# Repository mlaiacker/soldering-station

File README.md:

# Soldering Station for Weller Soldering Tips

https://www.weller-tools.com/eu/de/industrielles-loeten/produkte/loetspitzen/rtm-013-s

Power or Battery supply 10-14V DC up to 3A or so needed.

This project is based on the work of Martin Kumm.

http://www.martin-kumm.de/wiki/doku.php?id=05Misc:SMD_Solderstation

I made it simpler and cheaper. Instead of using an Arduino I use a ATmega8. This design doesn't use SMD instead a single sided PCB for easy assembly and cheap PCB production. The PCB is only 70x50mm. Instead of using two buttons to adjust the temperature I use a poti and optionally you can use a standard HD44780 compatible LCD to display temperatures. It runs on plain c (no arduino) and also includes supports a bootloader for easy firmware upgrade. The Bootloader has to be programmed befor soldering the mega8 into the PCB. The bootloader is activaded using the Boot pins on the PCB (short PD2 to ground)

http://mlaiacker.mooo.com/Elektronik/Soldering%20Station/

http://fpv-community.de/showthread.php?41335-DIY-SMD-L%F6tstation-Ersatz-f%FCr-%28WELLER%29

## PCB layout

[board layout pdf hardware/eagle/rt_solder_simple_V1.2.brd.pdf](hardware/eagle/rt_solder_simple_V1.2.brd.pdf?raw=true)

## Bill of Materials for PCB

[BOM as pdf](hardware/eagle/rt_solder_simple_V1.2.BOM.pdf?raw=true)

| Qty | Value        | Device          | Package      | Parts                | Description                 | Comment                       | Link |
| --- | ------------ | --------------- | ------------ | -------------------- | --------------------------- | ----------------------------- | ---- |
| 3   | 10nF         | C-EU050-035X075 | C050-035X075 | C6, C7, C8           | CAPACITOR,                  |                               |      |
| 5   | 100nF        | C-EU050-035X075 | C050-035X075 | C3, C4, C9, C10, C11 | CAPACITOR,                  |                               |      |
| 1   | TLC27L2ACP   | TLC27L2ACP      | DIL08        | IC3                  | DUAL OPERATIONAL AMPLIFIERS |                               |      |
| 1   | 22µH or 10R  | L-EU0207/10     | 0207/10      | L1                   | INDUCTOR,                   |                               |      |
| 1   | BOOT         | JP1E            | JP1          | JP2                  | JUMPER                      | to enable bootloader          |      |
| 1   | MEGA8-P      | MEGA8-P         | DIL28-3      | IC1                  | MICROCONTROLLER             | needs bootloader              |      |
| 1   | 2N7000 N-CH  | VN2222KM        | TO237        | Q1                   | N-Channel MOSFET            |                               |      |
| 1   | IRF5305 P-CH | IRF9530         | TO220BV      | Q3                   | P-CHANNEL POWER-MOS-FET     |                               |      |
| 1   | LCD          | PINHD-2X7       | 2X07         | JP1                  | PIN HEADER                  | optional                      |      |
| 1   | LED          | MA03-1          | MA03-1       | SV4                  | PIN HEADER                  |                               |      |
| 1   | POTI         | MA03-1          | MA03-1       | SV1                  | PIN HEADER                  | Poti to set temperatur 1K-50K |      |
| 1   | UART         | MA03-1          | MA03-1       | SV2                  | PIN HEADER                  | optional                      |      |
| 1   | 4.7µF 10V    | CPOL-EUE2.5-6   | E2,5-6       | C1                   | POLARIZED CAPACITOR         |                               |      |
| 2   | 470µF 16V    | CPOL-EUE3.5-10  | E3,5-10      | C2, C5               | POLARIZED CAPACITOR,        |                               |      |
| 1   | 100R         | R-EU_0207/10    | 0207/10      | R6                   | RESISTOR,                   |                               |      |
| 1   | 470R         | R-EU_0207/10    | 0207/10      | R2                   | RESISTOR,                   |                               |      |
| 1   | 68k          | R-EU_0207/10    | 0207/10      | R5                   | RESISTOR,                   |                               |      |
| 2   | 5k6          | R-EU_0207/10    | 0207/10      | R4, R7               | RESISTOR,                   |                               |      |
| 4   | 1k           | R-EU_0207/10    | 0207/10      | R3, R8, R11, R12     | RESISTOR,                   |                               |      |
| 1   | 47k          | R-EU_0207/10    | 0207/10      | bodge                | RESISTOR,                   | to fix tmperature measurement |      |
| 1   | 10M          | R-EU_0207/10    | 0207/10      | bodge                | RESISTOR,                   | to fix tmperature measurement |      |
| 1   | 10k          | R-EU_0207/10    | 0207/10      | bodge                | RESISTOR,                   | to add voltage measurement |      |
| 1   | 100k         | R-EU_0207/10    | 0207/10      | bodge                | RESISTOR,                   | to add voltage measurement |      |
| 1   | 78L05        | 78XXS           | 78XXS        | IC2                  | VOLTAGE REGULATOR           |                               |      |
| 1   | POWER        | W237-02P        | W237-132     | X1                   | WAGO SREW CLAMP             | optional                      |      |
| 1   | Solder       | W237-3E         | W237-3E      | X2                   | WAGO SREW CLAMP             | optional                      |      |

## Images

PCB<br>
 <br>
With nice enclosure and LCD<br>
 <br>
You can also just use this scale to set the temperature instead of the LCD
 <br>
Ask me for PCBs !! I had 10 made and some are available<br>
 <br>

## FAQ

### Hast du noch Platinen? 

ja noch: <br>
10 (2.4.2016)<br>
9 (5.4.2016)<br>
Ich kann auch gleich programmierten atmega8 und OPA und LCD dazu legen

### Was Kostet? 
10

### hex bauen?

```
make all
```

Das erstellen der main.hex geht über das Makefile mit "make all" dazu musst du den gcc avr Compiler installiert haben siehe dazu :http://www.mikrocontroller.net/articles/AVR-GCC

### flashen?

[for atmega 168](software/avr/main_atmega168.hex)

[for atmega 8](software/avr/main_atmega8.hex)

```
make program
```

Mit "make program" wird dann avrdude aufgerufen um über die serielle Schnittstelle ein neues Programm zu laden.
Dazu musst du wahrscheinlich den Port (com1) ändern im Makefile

```
AVRDUDE_PORT = com1 -b 38400 # programmer connected to serial device
```

Computer per TTL Seriell mit der Platine verbinden einen jumper auf die "Boot" pins stecken und einschalten dann wird der Bootloader aktiviert.

### bootloader ?

kopliziert. mit extra Adapter per ISP und dann mit "make programm_all" im bootloader Ordner. (avrdude und DIAMEX USB ISP bei mir)

### Wo bekomme ich IC3 her?

TLC 272 DIP bei reichelt

### Temperatur stimmt nicht

Die auf dem Display angezeigte Temperatur ist zu hoch bzw entspricht nicht der an der Lötspitze gemessenen. 
Bitte einen 47k Widerstand von Pin 3 an IC3 nach Masse löten und neue Software laden und wenn nötig
```C
#define TEMP_GAIN	(4980L)
#define TEMP_OFFSET	(-8)
```
anpassen.

 <br>

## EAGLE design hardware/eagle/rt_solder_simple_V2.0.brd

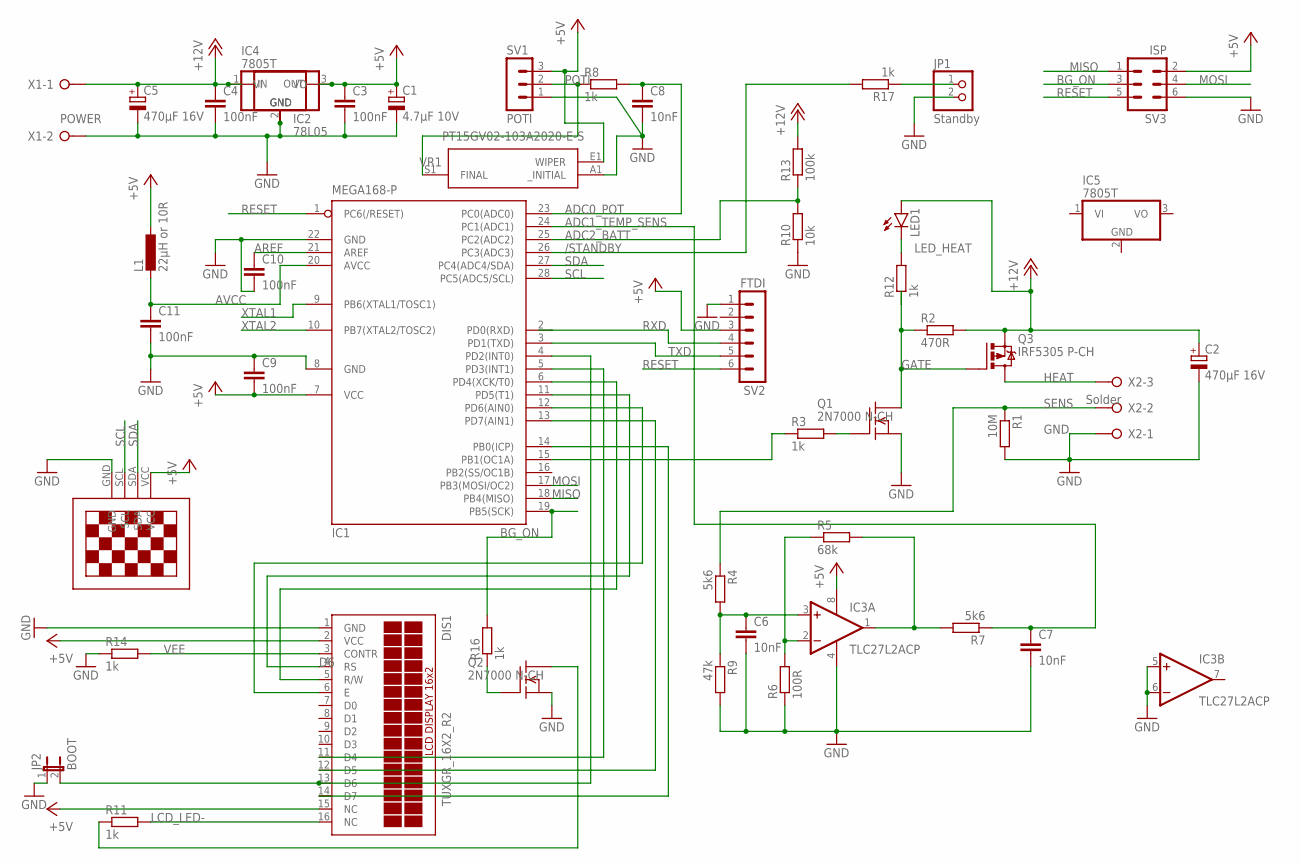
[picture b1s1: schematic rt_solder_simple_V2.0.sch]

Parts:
C1: 4.7µF 10V; E2,5-6
C2, C5: 470µF 16V; E3,5-10
C3, C4, C9, C10, C11: 100nF; C050-035X075
C6, C7, C8: 10nF; C050-035X075
DIS1: TUXGR_16X2_R2
IC1: MEGA168-P; DIL28-3
IC2: 78L05; 78XXS
IC3: TLC27L2ACP; DIL08
IC4, IC5: 7805T; TO220H
JP1: Standby; 1X02
JP2: BOOT; JP1
L1: 22µH or 10R; 0207/10
LED1: LED5MM
Q1, Q2: 2N7000 N-CH; TO237
Q3: IRF5305 P-CH; TO220BV
R1: 10M; 0207/10
R2: 470R; 0207/10
R3, R8, R11, R12, R14, R16, R17: 1k; 0207/10
R4, R7: 5k6; 0207/10
R5: 68k; 0207/10
R6: 100R; 0207/10
R9: 47k; 0207/10
R10: 10k; 0207/10
R13: 100k; 0207/10
SV1: POTI; MA03-1
SV2: FTDI; MA06-1
SV3: ISP; ML6
U$1: 13"OLED13"OLED; 1.3"OLED
VR1: PT15GV02-103A2020-E-S; PT15GV02103A2020ES
X1: POWER; W237-132
X2: Solder; W237-3E

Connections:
+5V: C1.+, C3.1, C9.2, DIS1.2 (VCC), IC1.7 (VCC), IC2.OUT, IC3.8 (VDD), IC4.3 (VO), L1.1, SV1.3, SV2.3, SV3.2, U$1.VCC, VR1.E1 (WIPER)
+12V: C2.+, C4.1, C5.+, IC2.IN, IC4.1 (VI), LED1.A, Q3.S, R2.2, R13.2, X1.1
/STANDBY: IC1.26 (PC3(ADC3)), R17.2
ADC0_POT: C8.1, IC1.23 (PC0(ADC0)), R8.2
ADC1_TEMP_SENS: C7.1, IC1.24 (PC1(ADC1)), R7.1
ADC2_BATT: IC1.25 (PC2(ADC2)), R10.2, R13.1
AREF: C10.1, IC1.21 (AREF)
AVCC: C11.1, IC1.20 (AVCC), L1.2
BG_ON: IC1.19 (PB5(SCK)), R16.2, SV3.3
D4: DIS1.11 (D4), IC1.5 (PD3(INT1))
D5: DIS1.12 (D5), IC1.13 (PD7(AIN1))
D6: DIS1.13 (D6), IC1.4 (PD2(INT0)), JP2.2
D7: DIS1.14 (D7), IC1.14 (PB0(ICP))
GATE: Q1.1 (D), Q3.G, R2.1, R12.1
GND: C1.-, C2.-, C3.2, C4.2, C5.-, C6.2, C7.2, C8.2, C9.1, C10.2, C11.2, DIS1.1 (GND), IC1.8 (GND), IC1.22 (GND), IC2.GND, IC3.4 (GND), IC3.5 (+IN), IC3.6 (-IN), IC4.2 (GND), JP1.2, JP2.1, Q1.3 (S), Q2.3 (S), R1.2, R6.1, R9.2, R10.1, R14.1, SV1.1, SV2.1, SV3.6, U$1.GND, VR1.A1 (_INITIAL), X1.2, X2.1
HEAT: Q3.D, X2.3
LCD_E: DIS1.6 (E), IC1.12 (PD6(AIN0))
LCD_LED-: DIS1.16 (NC), R11.2
LCD_RS: DIS1.4 (RS), IC1.11 (PD5(T1))
LCD_RW: DIS1.5 (R/W), IC1.6 (PD4(XCK/T0))
LED_HEAT: LED1.K (C), R12.2
MISO: IC1.18 (PB4(MISO)), SV3.1
MOSI: IC1.17 (PB3(MOSI/OC2)), SV3.4
unnamed: Q1.2 (G), R3.2
unnamed: C6.1, IC3.3 (+IN), R4.2, R9.1
unnamed: IC3.2 (-IN), R5.1, R6.2
unnamed: IC3.1 (OUT), R5.2, R7.2
unnamed: IC1.15 (PB1(OC1A)), R3.1
unnamed: Q2.2 (G), R16.1
unnamed: JP1.1, R17.1
unnamed: Q2.1 (D), R11.1
POTI: R8.1, SV1.2, VR1.S1 (FINAL)
RESET: IC1.1 (PC6(/RESET)), SV2.6, SV3.5
RXD: IC1.2 (PD0(RXD)), SV2.4
SCL: IC1.28 (PC5(ADC5/SCL)), U$1.SCL
SDA: IC1.27 (PC4(ADC4/SDA)), U$1.SDA
SENS: R1.1, R4.1, X2.2
TXD: IC1.3 (PD1(TXD)), SV2.5
VEE: DIS1.3 (CONTR), R14.2
XTAL1: IC1.9 (PB6(XTAL1/TOSC1))
XTAL2: IC1.10 (PB7(XTAL2/TOSC2))

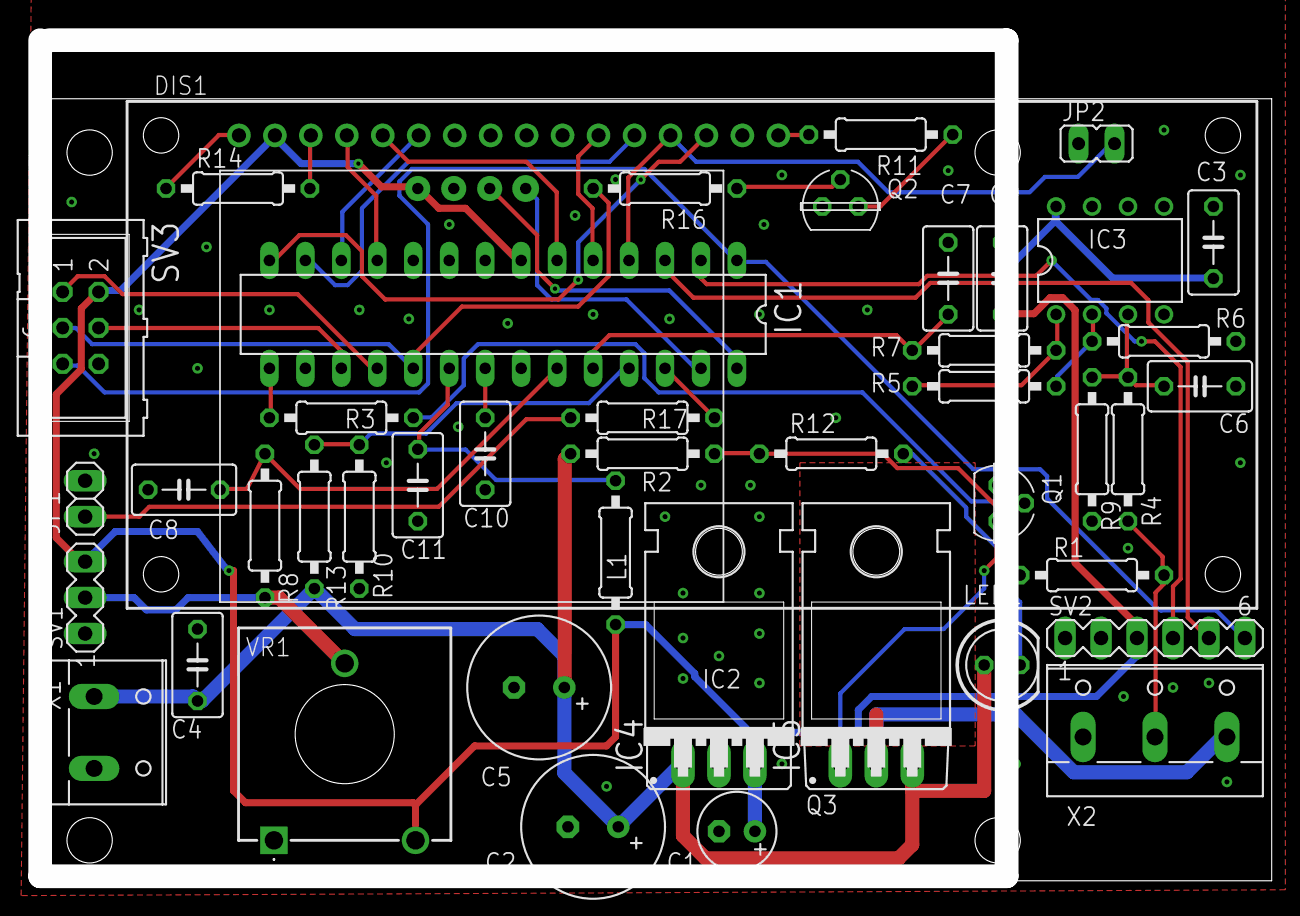
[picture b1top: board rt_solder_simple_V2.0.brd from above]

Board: 2 copper layers, 86.1 x 59.1 mm, 47 parts (0 on the bottom side), 39 nets.

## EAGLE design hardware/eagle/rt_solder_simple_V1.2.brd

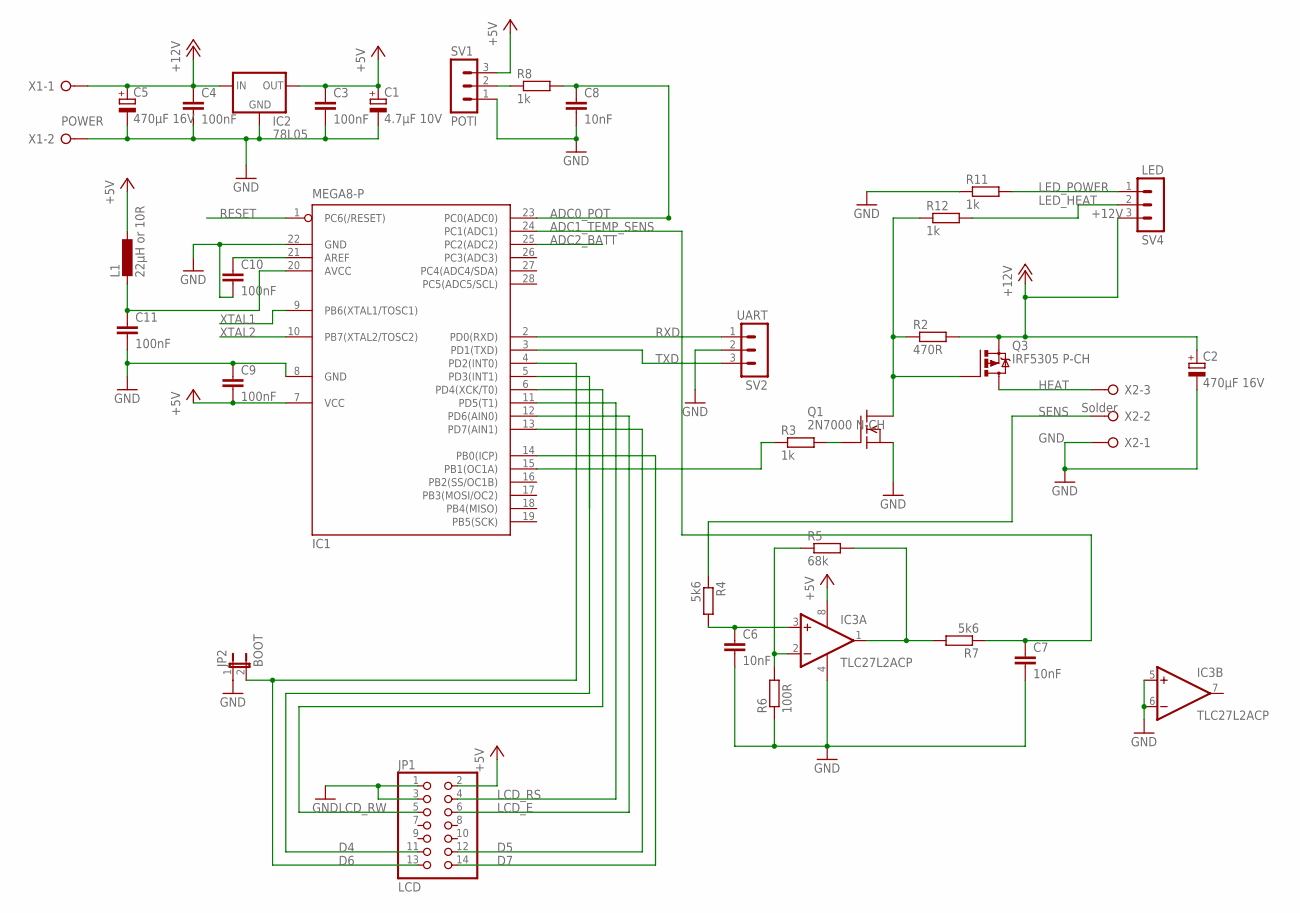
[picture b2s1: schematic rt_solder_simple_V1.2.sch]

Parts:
C1: 4.7µF 10V; E2,5-6
C2, C5: 470µF 16V; E3,5-10
C3, C4, C9, C10, C11: 100nF; C050-035X075
C6, C7, C8: 10nF; C050-035X075
IC1: MEGA8-P; DIL28-3
IC2: 78L05; 78XXS
IC3: TLC27L2ACP; DIL08
JP1: LCD; 2X07
JP2: BOOT; JP1
L1: 22µH or 10R; 0207/10
Q1: 2N7000 N-CH; TO237
Q3: IRF5305 P-CH; TO220BV
R2: 470R; 0207/10
R3, R8, R11, R12: 1k; 0207/10
R4, R7: 5k6; 0207/10
R5: 68k; 0207/10
R6: 100R; 0207/10
SV1: POTI; MA03-1
SV2: UART; MA03-1
SV4: LED; MA03-1
X1: POWER; W237-132
X2: Solder; W237-3E

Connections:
+5V: C1.+, C3.1, C9.2, IC1.7 (VCC), IC2.OUT, IC3.8 (VDD), JP1.2, L1.1, SV1.3
+12V: C2.+, C4.1, C5.+, IC2.IN, Q3.S, R2.2, SV4.3, X1.1
ADC0_POT: C8.1, IC1.23 (PC0(ADC0)), R8.2
ADC1_TEMP_SENS: C7.1, IC1.24 (PC1(ADC1)), R7.1
ADC2_BATT: IC1.25 (PC2(ADC2))
D4: IC1.5 (PD3(INT1)), JP1.11
D5: IC1.13 (PD7(AIN1)), JP1.12
D6: IC1.4 (PD2(INT0)), JP1.13, JP2.2
D7: IC1.14 (PB0(ICP)), JP1.14
GND: C1.-, C2.-, C3.2, C4.2, C5.-, C6.2, C7.2, C8.2, C9.1, C10.2, C11.2, IC1.8 (GND), IC1.22 (GND), IC2.GND, IC3.4 (GND), IC3.5 (+IN), IC3.6 (-IN), JP1.1, JP1.3, JP2.1, Q1.3 (S), R6.1, R11.1, SV1.1, SV2.2, X1.2, X2.1
HEAT: Q3.D, X2.3
LCD_E: IC1.12 (PD6(AIN0)), JP1.6
LCD_RS: IC1.11 (PD5(T1)), JP1.4
LCD_RW: IC1.6 (PD4(XCK/T0)), JP1.5
LED_HEAT: R12.2, SV4.2
LED_POWER: R11.2, SV4.1
unnamed: Q1.1 (D), Q3.G, R2.1, R12.1
unnamed: Q1.2 (G), R3.2
unnamed: C6.1, IC3.3 (+IN), R4.2
unnamed: IC3.2 (-IN), R5.1, R6.2
unnamed: IC3.1 (OUT), R5.2, R7.2
unnamed: IC1.15 (PB1(OC1A)), R3.1
unnamed: R8.1, SV1.2
unnamed: C11.1, IC1.20 (AVCC), L1.2
unnamed: C10.1, IC1.21 (AREF)
RESET: IC1.1 (PC6(/RESET))
RXD: IC1.2 (PD0(RXD)), SV2.1
SENS: R4.1, X2.2
TXD: IC1.3 (PD1(TXD)), SV2.3
XTAL1: IC1.9 (PB6(XTAL1/TOSC1))
XTAL2: IC1.10 (PB7(XTAL2/TOSC2))

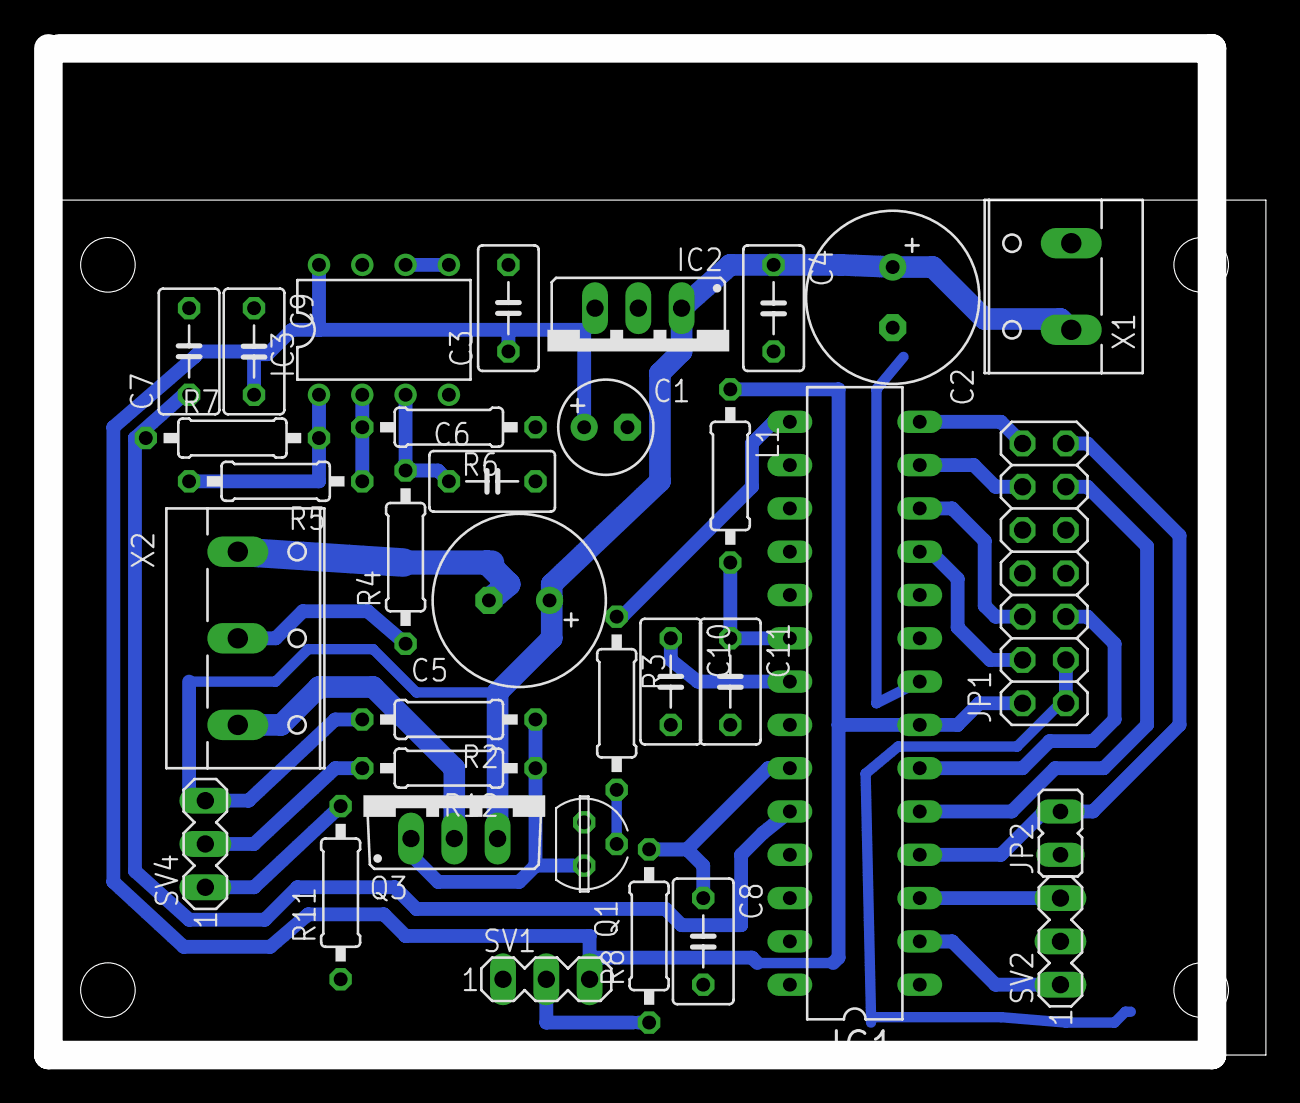
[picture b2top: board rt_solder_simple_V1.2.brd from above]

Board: 2 copper layers, 70.6 x 59.1 mm, 33 parts (0 on the bottom side), 27 nets.

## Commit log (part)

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2015-03-21 :space_invader: Added .gitattributes & .gitignore files
2015-03-21 initial software and images
2015-03-21 readme
2015-03-21 hardware eagle files
2015-03-21 readme update
2015-03-21 missing avr files
2015-12-03 scale template added and readme update
2015-12-05 bootloader and main prog flash and changed the measurment timing
    also standby detection changed
2015-12-06 lcd pictures 2 line lcd support
2015-12-06 chaged temperature measurement and lcd display stuff
    added define for lcd 2x16 or 1x20
2016-04-03 chages for acr-gcc toolchain from atmel
    Makefile stuff
2016-04-07 added comments abnd some defines
2016-04-07 fix integer overflow
2016-04-07 more defines and comments
2016-04-23 added temperature gain and offset constants
2016-04-23 Temperature gain and offset adjustment
2016-04-23 changed standby detection and added timeout value display
2016-04-23 added image of pached resistor
2017-02-16 build date and git version
2017-02-16 version tag
2017-02-16 jump to bootloader
2020-06-16 git version display at startup and input voltage mointoring added, bootloader fixes, timout counter display
2024-02-10 part list added
2024-02-10 added board pdf
2024-02-10 rotated pcb image to match board layout in eagle orientation and added link to brd PDF
2024-02-10 README.md
2024-02-10 added BOM pdf
2024-02-10 added bom pdf to README.md
2024-02-10 README.md changed to relative paths and added main_atmega168.hex build
2024-02-10 update README.md for link to hex files
2024-02-10 README.md include link to weller
2024-02-10 fixed programming and aadded more bodge resistors for voltage mesurement
2024-02-10 README.md and added solder tip pinout
2024-02-10 README.md link fixed
2024-02-10 README.md fixed 100k resistor
2024-10-04 update and added uart menu
2024-10-04 added avrdude.conf
